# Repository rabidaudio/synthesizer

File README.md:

# Synth

> These are my custom modules for a from-scratch [Eurorack](https://en.wikipedia.org/wiki/Eurorack) analog synthesizer.

https://rabid.audio/projects/synth

## Modules

1. [Amplifier](amp)
  - LM13700
  - matched-pair PNP exponential converter
  - CV of 10V -> Gain=1
  - CV of <=0V -> Gain=\~0, 6 decades below Gain=1
  - allow overdrive to Gain=2
    - ideally this would begin to clip
  - mixdown
    - mono - full mix -> left and right
    - stereo split - A+C->left B+D->right
  - Direct stereo input jack
    - mix arbitrary signal with mixdown
    - e.g. for accepting signals from other synths
2. [Oscillator](vco)
  - 0-10V, 1V/octave, A0 to A10
  - Square/Triangle core via LM13700
  - Waveshapper for triangle -> sine
  - PWM control
    - triangle wave applied to comparator with CV controlling reference. Triangle wave means CV is linear
  - abs(triangle) can be used for 2x square
    - adds a lot of parts for little benefit
  - blending shapes isn't useful here, since we could use other oscillators for that
  - Option to sync with another osc?
    - in theory, grounding osc at a regular interval would reset the osc over and over, effectively changing it's frequency
  - CV control for shape?
  - Room for more shapes
    - white noise?
    - PDS
      - https://en.wikipedia.org/wiki/Phase_distortion_synthesis
      - a bit of wild harmonics
      - multiplication techniques
        - log/antilog
        - https://en.wikipedia.org/wiki/Gilbert_cell
        - AD633 ($11-$13 /unit on DigiKey!?)
        - EL4450C ($4/unit on Digikey but out of stock). It's a little more awkward to use since it's max differerential input voltage for linearity is 2V
      - the hard part will be the "slightly higher frequency" bit
        - perhaps instead you have another osc (555?) running at a fixed frequency and clipping the sine
        - square PWM control could also adjust this clip frequency
      - In Max you do PDS by `kink~`-ing a `phasor~` and using that to drive the phase of `cycle~`. Kink is somewhat straightforward to do - use a comparator to adjust the charge current after a threshold. But how you drive a sine wave phase with that I'm not sure
    - down ramp wave with just a JFET
      - up ramp wave probably needs another JFET and an inverter
    - sub octave
      - theory and example circuit: http://www.valvewizard.co.uk/uboat.html
    - octave
      - full wave rectifier
    - multiplying the triangle with a square wave with different phases and pulse-widths gives some neat sounds
    - polynomial
      - The EL4450C datasheet describes using a multiplier ic to create a polynomial of the form (k1 v^2 + v) / k2
      - it sounds like crap on a triangle wave and does nothing for a square wave, but it adds a nice second harmonic to a sine wave
      - from experiments in Max, good values are k1=1.5-2.5, k2=2
      - but at that point, should you just use 2 oscillators?
3. [A/D/S/R envelope](adsr)
  - 4 envelopes required for 4-voice polyphony
  - wired to VCA by default
  - save surface area with 1 set of ADSR controls for a pair of envelopes
  - fully modular means you could borrow one for VCF instead, or send to both VCA and VCF
4. Filter
  -  4P LP(/HP?)
  - Cutoff frequency control has same range as oscillator
    - 0-10V, 1V/octave, A0 to A10
  - filter we designed for class
    - standard vactrols are available on Thonk
  - CV control of cutoff + resonance
  - Default to track cutoff with VCO-CV
  - individual filter knobs, plus a global knob for filter sweeps
5. [Utilities](utils)
  - Buffer, Sum, Attenuate, Invert, Gate
  - Could be all-in one
    - A input (default ground)
    - B input (default ground)
    - level knob attenuator
    - gate digital CV in, default on
    - `(A+B)*level*gate` output
    - `-(A+B)*level*gate` output
    - Constant CV out if A and B disconnected

Bitcrusher?
4 filters or one?
Noise?
Clock?
Headphone output no longer required
2D mixer?

## TODO

- utility module
  - [x] Verify on breadboard
  - [x] design PCB
  - [x] order parts
  - [x] come up with a cute name
  - [x] design front panel
  - [x] assemble Rev. A PCB
    - bend the regulators first
    - plenty of 4066s
    - flip orientation of power connector
    - pot orientation - both channels:
      - right side (facing) to inside of board (from top)
      - left side (facing) to outside of board (from top)
  - [x] test with Neutron
    - constant output is only 9 to -7.8
    - high noise when used as a buffer
      - perhaps input signal is clipping?
      - white noise when the gain is turned down
  - [x] adjust design for Rev. B
  - [x] assemble Rev. B proto board
  - fix prototype issues
    - [ ] sum pot is backwards
    - [ ] a bit of noise on the constant output near the center
    - [ ] verify output levels
    - [ ] hard click on gate
      - needs a LPF?
  - [ ] assemble Rev. B PCB
  - [ ] manufacture front panel
  - [ ] assemble module
- VCA
  - [x] Confirm amp on breadboard, finalize CV levels
  - [x] figure out where tuning trimmers are needed
  - [x] build prototype
  - fix prototype issues
    - [ ] output is too quiet for headphones, need about 2x gain
    - [ ] CV range is too wide, adjust scaling for faster change in db/V
  - [ ] finish PCB schematic for complete amplifier
  - [ ] Create PCB
  - [ ] design front panel
  - [ ] manufacture front panel
  - [ ] assemble module
- VCO
  - [ ] design core
    - [x] core osc - square/triangle
    - [x] wave shaper (sine)
    - [x] pwm control
    - [ ] additional shape
    - [x] shape selection
  - [x] Confirm amp on breadboard, finalize CV levels
  - fix breadboard test issues
    - [ ] pitch is very sensitive to power supply noise
    - [ ] tuning is rather difficult
  - [ ] Build prototype
  - fix prototype issues
    - TBD
  - [ ] design PCB
  - [ ] Create PCB
  - [ ] design front panel
  - [ ] manufacture front panel
  - [ ] assemble module
- Envelope
  - [x] design in SPICE
  - [ ] verify on breadboard
  - [ ] build prototype
  - fix prototype issues
    - TBD
  - [ ] design PCB
  - [ ] Create PCB
  - [ ] design front panel
  - [ ] manufacture front panel
  - [ ] assemble module
- VCF
  - TBD
- build tools
  - [x] tiny Breakout pcbs for headphone jacks
  - ~~transistor matcher circuit~~
    - bought matched pair BJTs instead
  - [x] quantized selector with hysteresis

## License

Schematics, board layouts, documentation, etc. is licensed under [Creative Commons Attribution-NonCommercial-ShareAlike 4.0 International License](http://creativecommons.org/licenses/by-nc-sa/4.0/).

If you're interested in commercial use, please ask first.

Any source code is licensed under [MIT](SOFTWARE_LICENSE).

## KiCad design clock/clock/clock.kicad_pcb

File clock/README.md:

# The Count

## [Writeup and documentation](https://rabid.audio/projects/synth/clk/)

## Features

- BPM from 15 to 400
- two outputs with relative rates
- 3-digit LED 7-segment display
- swing control
- tap tempo
- CV in
- pause
- save/load/reset settings

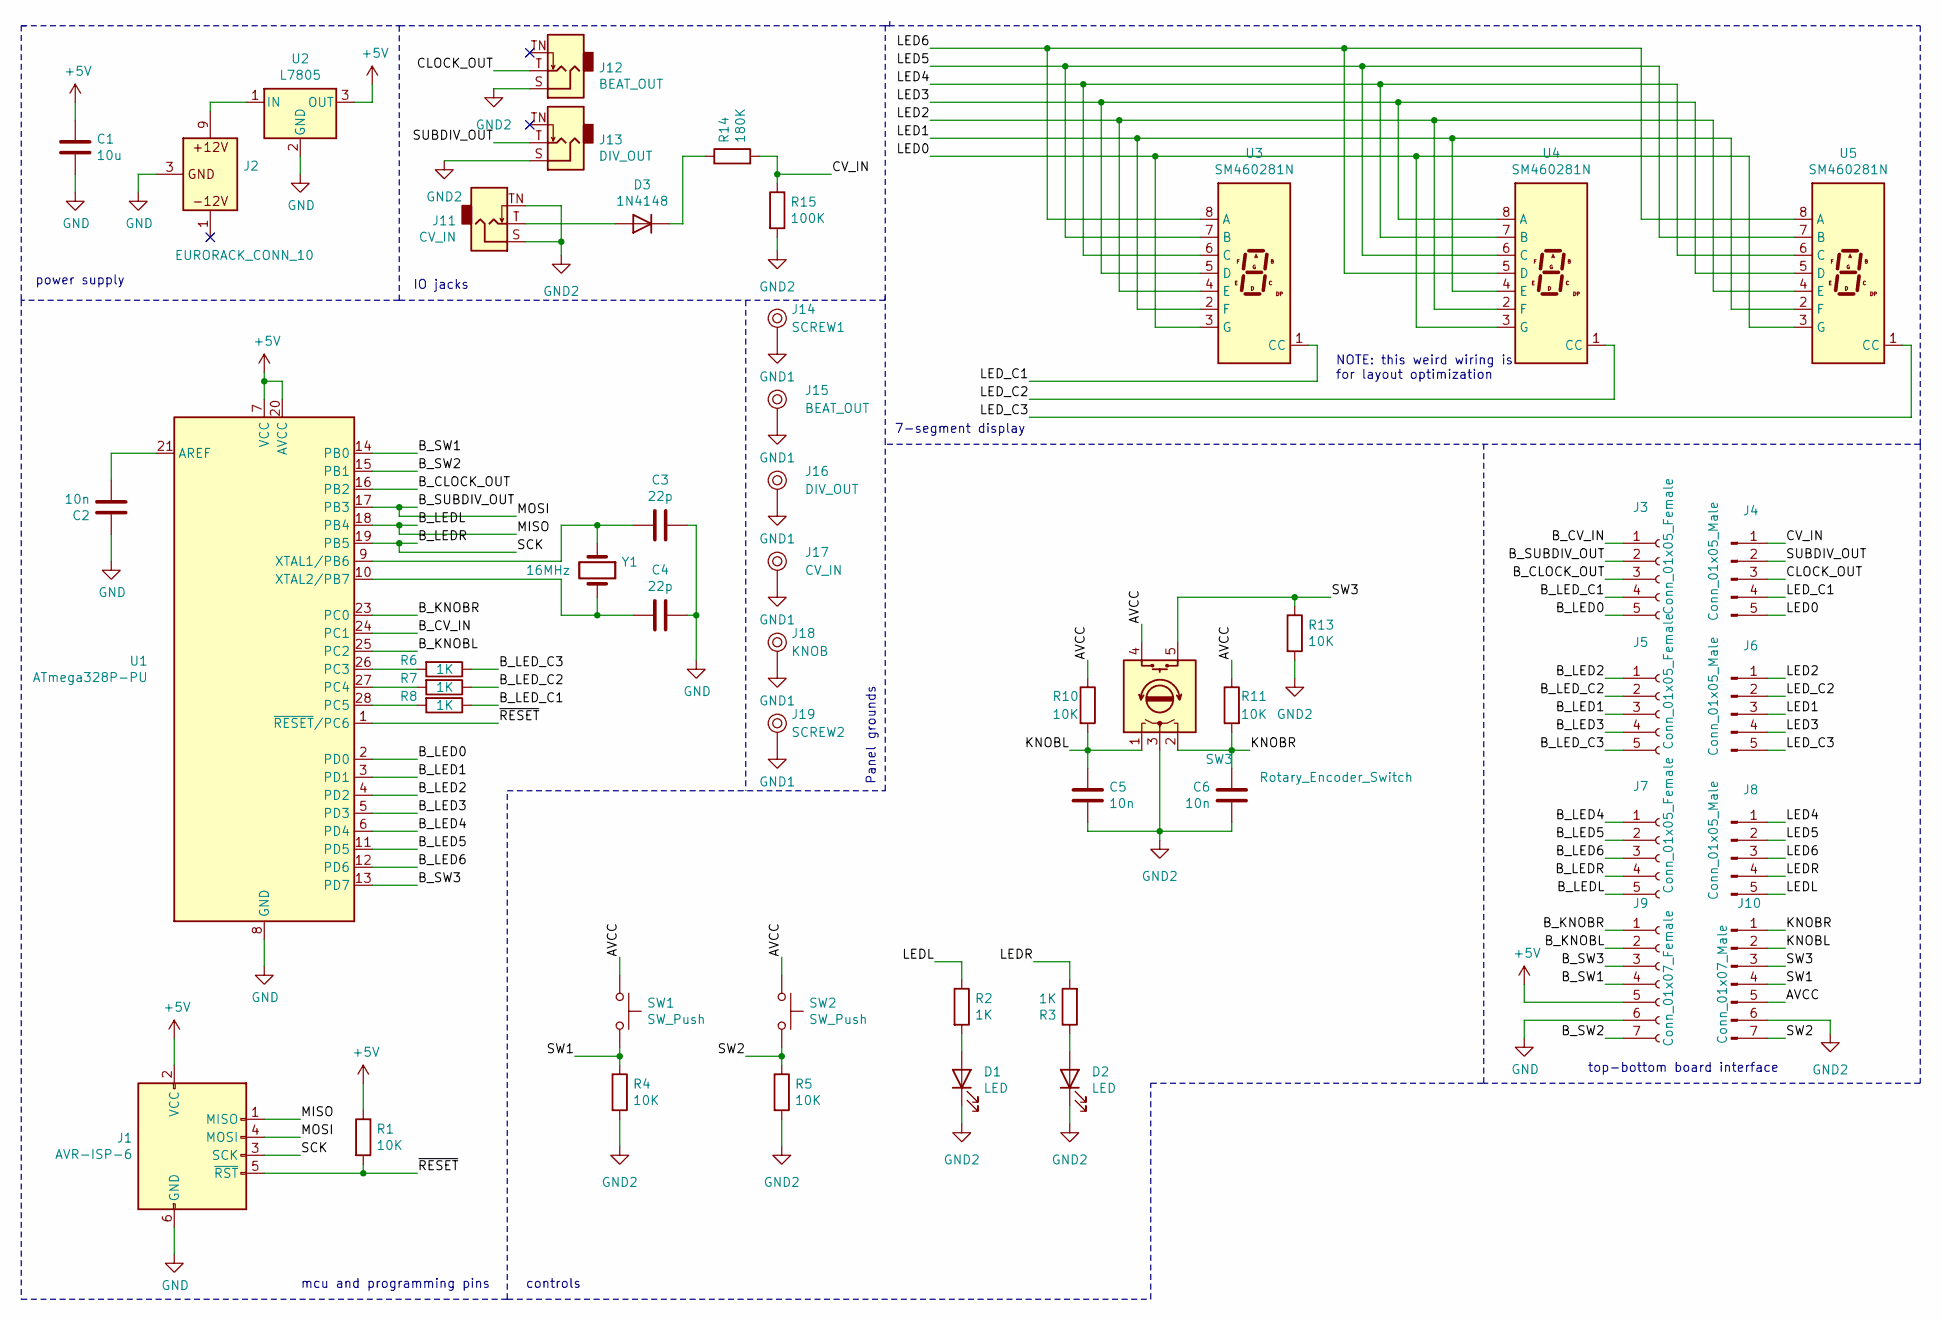
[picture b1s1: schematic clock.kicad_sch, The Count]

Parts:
C1: 10u; CP_Radial_Tantal_D4.5mm_P2.50mm
C2, C5, C6: 10n; C_Rect_L7.0mm_W3.5mm_P5.00mm
C3, C4: 22p; C_Rect_L7.0mm_W3.5mm_P5.00mm
D1, D2: LED; LED_D3.0mm
D3: 1N4148; D_T-1_P5.08mm_Horizontal
J1: AVR-ISP-6; PinHeader_2x03_P2.54mm_Vertical
J2: EURORACK_CONN_10; EURORACK_10_IDC
J3, J5, J7: Conn_01x05_Female; PinSocket_1x05_P2.54mm_Vertical
J4, J6, J8: Conn_01x05_Male; PinHeader_1x05_P2.54mm_Vertical
J9: Conn_01x07_Female; PinSocket_1x07_P2.54mm_Vertical
J10: Conn_01x07_Male; PinHeader_1x07_P2.54mm_Vertical
J11: CV_IN; Jack_3.5mm_QingPu_WQP-PJ398SM_Vertical_CircularHoles
J12: BEAT_OUT; Jack_3.5mm_QingPu_WQP-PJ398SM_Vertical_CircularHoles
J13: DIV_OUT; Jack_3.5mm_QingPu_WQP-PJ398SM_Vertical_CircularHoles
J14: SCREW1; eurorack_screw_hole
J15: BEAT_OUT; thonkiconn_hole
J16: DIV_OUT; thonkiconn_hole
J17: CV_IN; thonkiconn_hole
J18: KNOB; knob_hole
J19: SCREW2; eurorack_screw_hole
R1, R4, R5, R10, R11, R13: 10K; R_Axial_DIN0207_L6.3mm_D2.5mm_P2.54mm_Vertical
R2, R3, R6, R7, R8: 1K; R_Axial_DIN0207_L6.3mm_D2.5mm_P2.54mm_Vertical
R14: 180K; R_Axial_DIN0207_L6.3mm_D2.5mm_P2.54mm_Vertical
R15: 100K; R_Axial_DIN0207_L6.3mm_D2.5mm_P2.54mm_Vertical
SW1, SW2: SW_Push; SW_PUSH_6mm
SW3: Rotary_Encoder_Switch; RotaryEncoder_Bourns_PEC11R_Vertical_Switch
U1: ATmega328P-PU; DIP-28_W7.62mm
U2: L7805; TO-220-3_Vertical
U3, U4, U5: SM460281N; SM460281N_ARKLED_0.28mm_CC_7-segment_LED
Y1: 16MHz; Crystal_HC50_Vertical

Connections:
+5V: C1.1, J1.2 (VCC), J9.5, R1.1, U1.7 (VCC), U1.20 (AVCC), U2.3 (OUT)
/AVCC: J10.5, R10.1, R11.1, SW1.1, SW2.1, SW3.4 (S1)
/B_CLOCK_OUT: J3.3, U1.16 (PB2)
/B_CV_IN: J3.1, U1.24 (PC1)
/B_KNOBL: J9.2, U1.25 (PC2)
/B_KNOBR: J9.1, U1.23 (PC0)
/B_LED0: J3.5, U1.2 (PD0)
/B_LED1: J5.3, U1.3 (PD1)
/B_LED2: J5.1, U1.4 (PD2)
/B_LED3: J5.4, U1.5 (PD3)
/B_LED4: J7.1, U1.6 (PD4)
/B_LED5: J7.2, U1.11 (PD5)
/B_LED6: J7.3, U1.12 (PD6)
/B_LEDL: J1.1 (MISO), J7.5, U1.18 (PB4)
/B_LEDR: J1.3 (SCK), J7.4, U1.19 (PB5)
/B_LED_C1: J3.4, R8.1
/B_LED_C2: J5.2, R7.1
/B_LED_C3: J5.5, R6.1
/B_SUBDIV_OUT: J1.4 (MOSI), J3.2, U1.17 (PB3)
/B_SW1: J9.4, U1.14 (PB0)
/B_SW2: J9.7, U1.15 (PB1)
/B_SW3: J9.3, U1.13 (PD7)
/CLOCK_OUT: J4.3, J12.T
/CV_IN: J4.1, R14.2, R15.1
/KNOBL: C5.1, J10.2, R10.2, SW3.1 (A)
/KNOBR: C6.1, J10.1, R11.2, SW3.2 (B)
/LED0: J4.5, U3.3 (G), U4.3 (G), U5.3 (G)
/LED1: J6.3, U3.2 (F), U4.4 (E), U5.2 (F)
/LED2: J6.1, U3.4 (E), U4.2 (F), U5.4 (E)
/LED3: J6.4, U3.5 (D), U4.8 (A), U5.5 (D)
/LED4: J8.1, U3.6 (C), U4.7 (B), U5.6 (C)
/LED5: J8.2, U3.7 (B), U4.6 (C), U5.7 (B)
/LED6: J8.3, U3.8 (A), U4.5 (D), U5.8 (A)
/LEDL: J8.5, R2.1
/LEDR: J8.4, R3.2
/LED_C1: J4.4, U3.1 (CC)
/LED_C2: J6.2, U4.1 (CC)
/LED_C3: J6.5, U5.1 (CC)
/SUBDIV_OUT: J4.2, J13.T
/SW1: J10.4, R4.1, SW1.2
/SW2: J10.7, R5.1, SW2.2
/SW3: J10.3, R13.1, SW3.5 (S2)
/~RESET: J1.5 (~RST), R1.2, U1.1 (~RESET/PC6)
GND: C1.2, C2.1, C3.1, C4.1, J1.6 (GND), J2.3 (GND), J9.6, U1.8 (GND), U1.22 (GND), U2.2 (GND)
GND1: J14.1, J15.1, J16.1, J17.1, J18.1, J19.1
GND2: C5.2, C6.2, D1.1 (K), D2.1 (K), J10.6, J11.S, J11.TN, J12.S, J13.S, R4.2, R5.2, R13.2, R15.2, SW3.3 (C)
unnamed: C2.2, U1.21 (AREF)
unnamed: C3.2, U1.9 (XTAL1/PB6), Y1.1
unnamed: C4.2, U1.10 (XTAL2/PB7), Y1.2
unnamed: D1.2 (A), R2.2
unnamed: D2.2 (A), R3.1
unnamed: D3.1 (K), R14.1
unnamed: D3.2 (A), J11.T
unnamed: J2.9 (12V_P), U2.1 (IN)
unnamed: R6.2, U1.26 (PC3)
unnamed: R7.2, U1.27 (PC4)
unnamed: R8.2, U1.28 (PC5)

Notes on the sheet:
NOTE: this weird wiring is for layout optimization
7-segment display
Panel grounds
top-bottom board interface
power supply
mcu and programming pins
IO jacks
controls

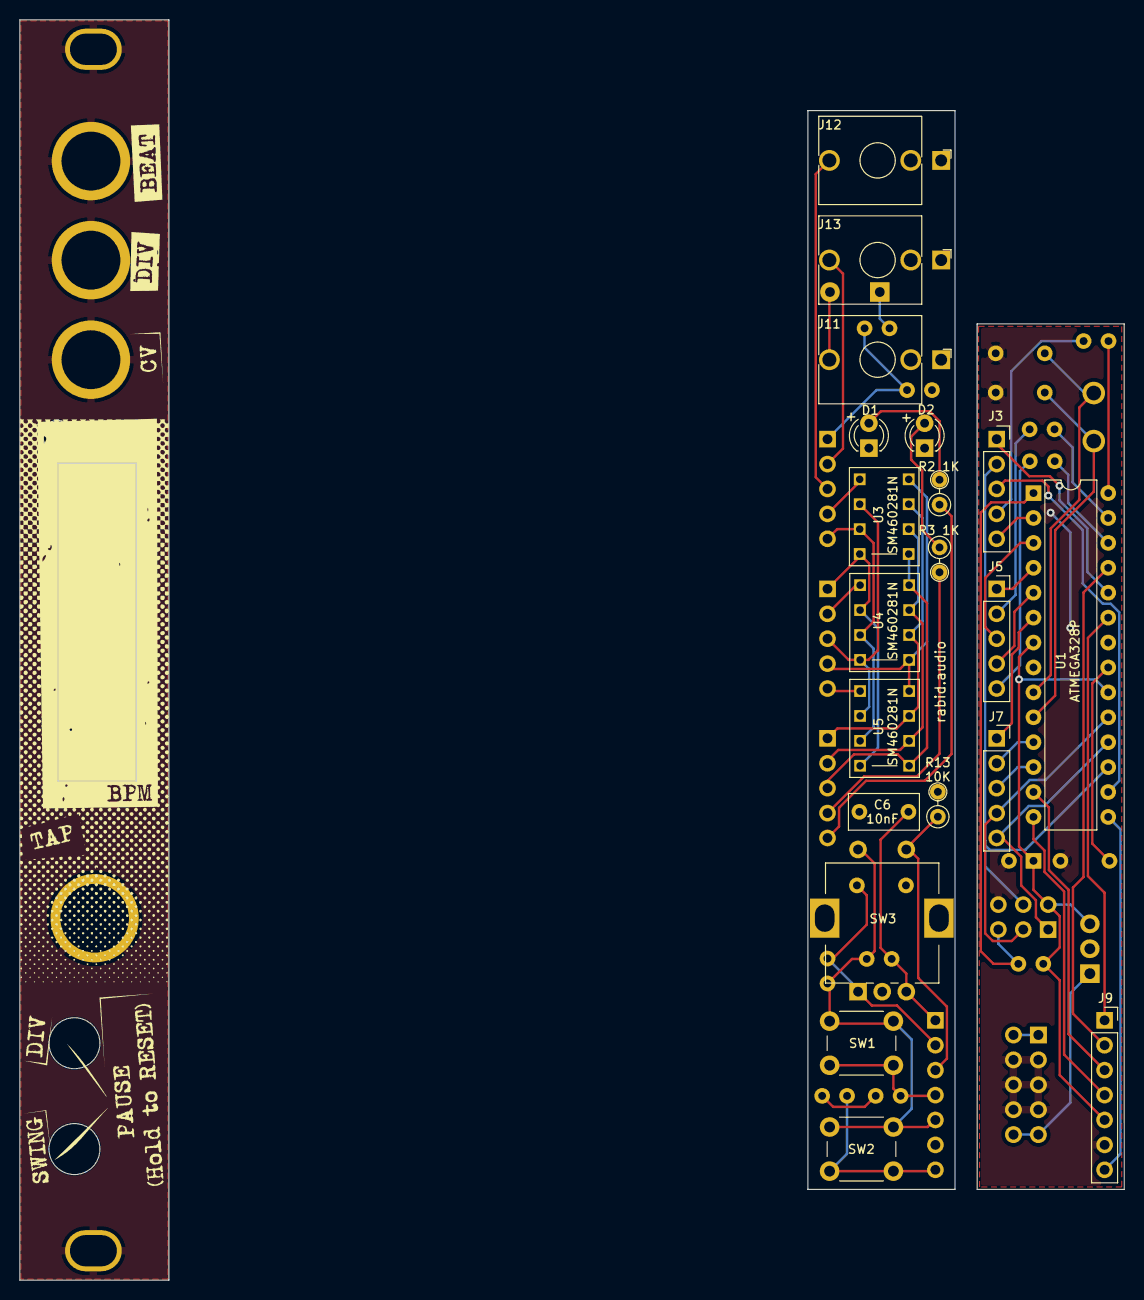
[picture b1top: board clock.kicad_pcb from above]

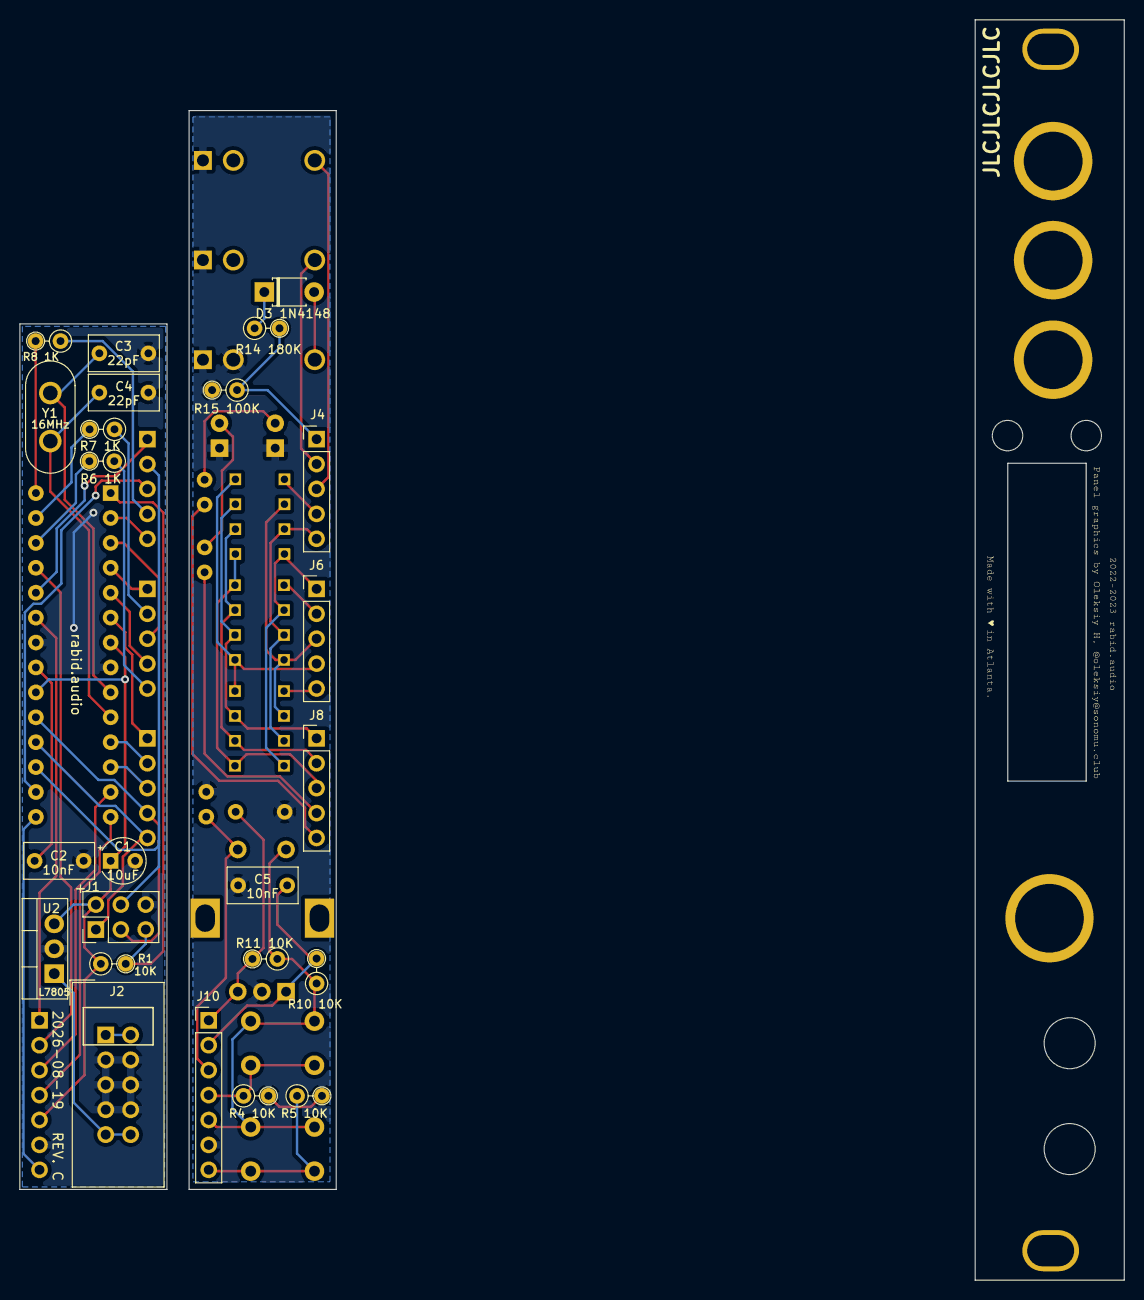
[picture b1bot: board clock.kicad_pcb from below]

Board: 2 copper layers, 112.6 x 128.5 mm, 50 parts (24 on the bottom side), 57 nets.

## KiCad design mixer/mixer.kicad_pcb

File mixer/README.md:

6-8 channels

vertical faders
Mute and solo buttons

stereo and pan?

Aux send/return (x2?)
EQ?

No CV?

Digital

cypress?

Op-amps in, round-robin sampling? Codec?

Per channel:
- in jack
- Fader
- mute btn+led
- solo btn+led
- Aux send knob
- Pan knob
- Tone knob (center detent)

Master:
- aux return jack x2
- out jack x2
- fader
- Aux return knob

maybe sets of 4 channels, plus master - with ribbon
- each has a single mix with direct in mixdown, allowing infinite daisy chain
  - -> prev in x2
  - mixdown x2 ->
  - mute/solo bus - SPI? <->
  - Power (from master)

- Master is analog mixer: last mixdown plus aux, through master fader and out

M_Switch
S_Switch
~Global_Solo (open drain, low if any solos)

M_LED = M_Switch && ~Global_Solo
S_LED = S_Switch
Global_Solo = Global_Solo || S_Switch
Channel Muted = M_Switch || (Global_Solo && !S_Switch)

https://docs.google.com/spreadsheets/d/1g7xjcmLrPR7thaU7WiNtqLLgusEtm41Zfw6h4pZd12A/edit?gid=347525464#gid=347525464

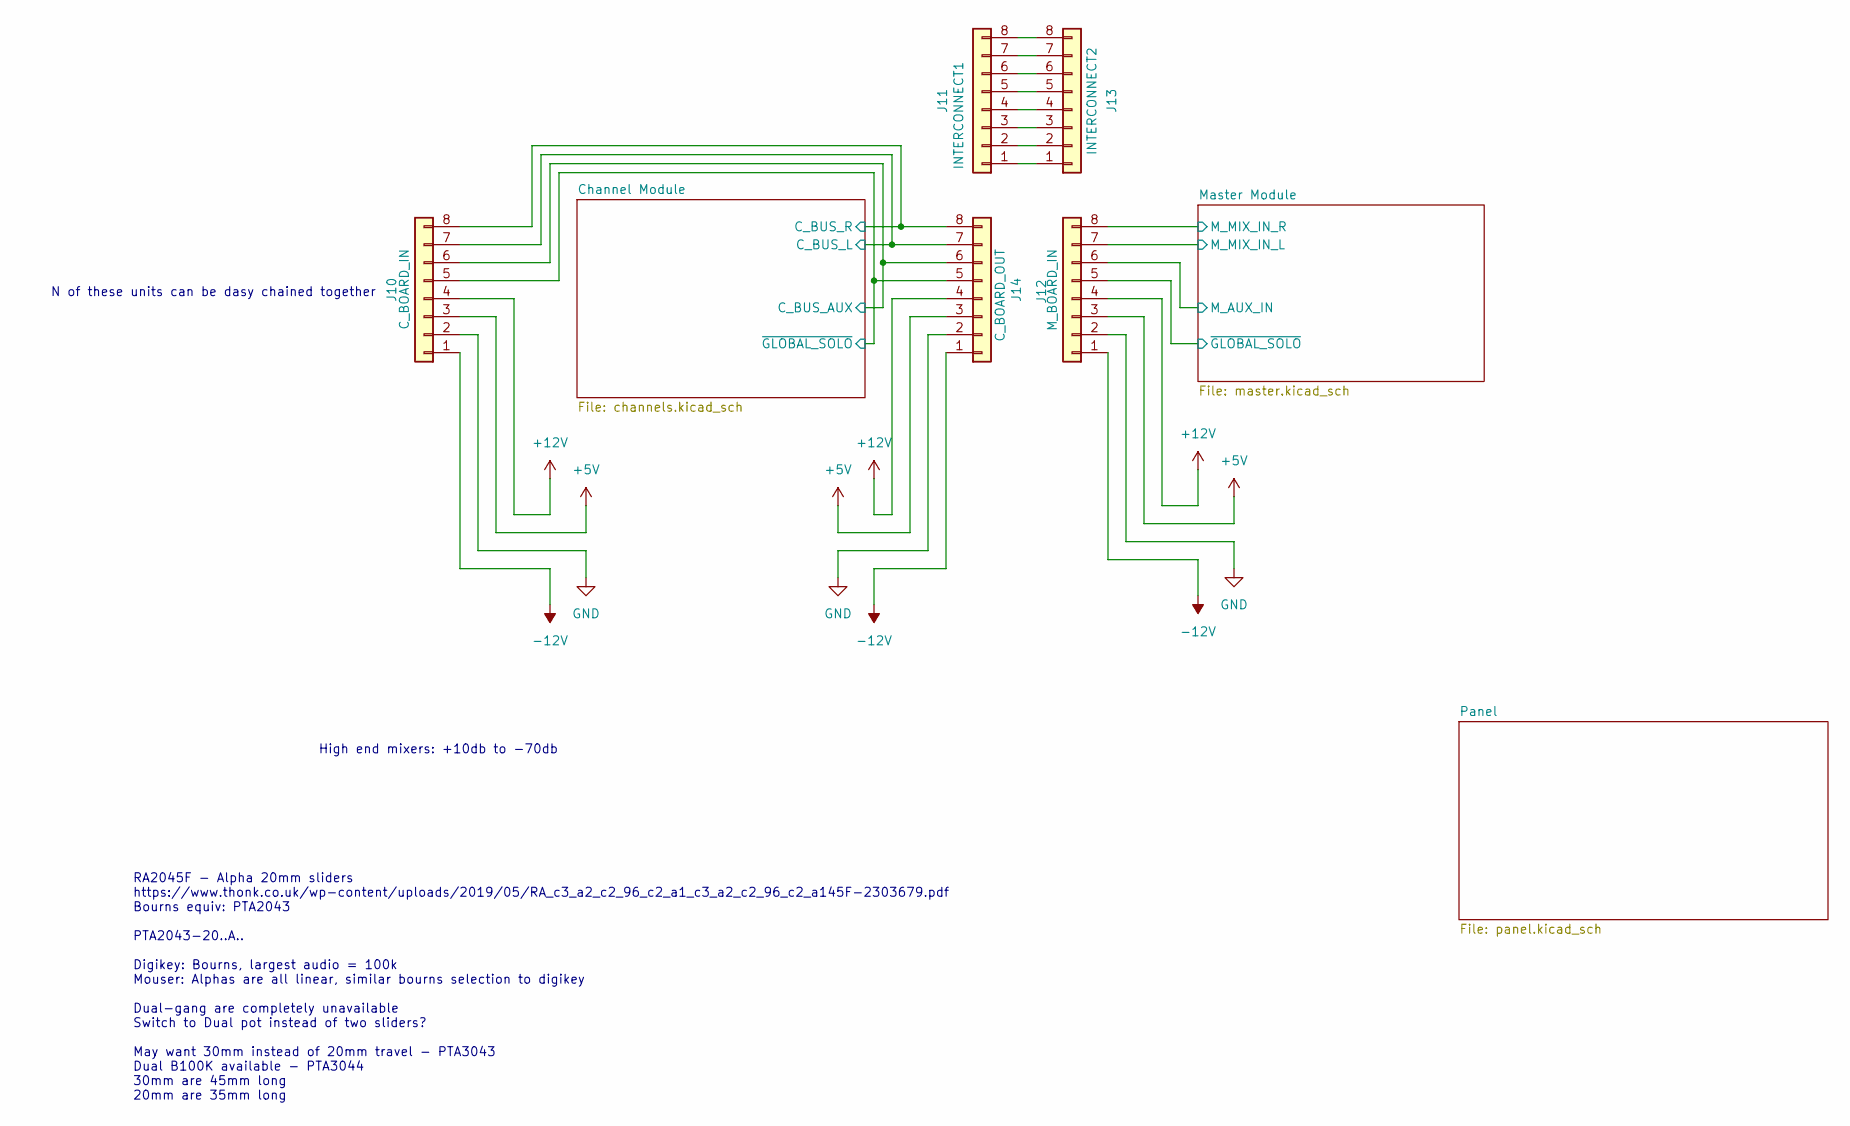
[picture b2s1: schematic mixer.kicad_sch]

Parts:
J10: C_BOARD_IN; PinSocket_1x08_P1.27mm_Vertical
J11: INTERCONNECT1; PinHeader_1x08_P1.27mm_Vertical
J12: M_BOARD_IN; PinSocket_1x08_P1.27mm_Vertical
J13: INTERCONNECT2; PinHeader_1x08_P1.27mm_Vertical
J14: C_BOARD_OUT; PinSocket_1x08_P1.27mm_Vertical

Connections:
+5V: J10.3, J12.3, J14.3; also elsewhere on the board
+12V: J10.4, J12.4, J14.4; also elsewhere on the board
-12V: J10.1, J12.1, J14.1; also elsewhere on the board
/Channel Module/C_BUS_AUX: J10.6, J14.6; also elsewhere on the board
/Channel Module/C_BUS_L: J10.7, J14.7; also elsewhere on the board
/Channel Module/C_BUS_R: J10.8, J14.8; also elsewhere on the board
/Channel Module/~GLOBAL_SOLO: J10.5, J14.5; also elsewhere on the board
/Master Module/M_AUX_IN: J12.6; also elsewhere on the board
/Master Module/M_MIX_IN_L: J12.7; also elsewhere on the board
/Master Module/M_MIX_IN_R: J12.8; also elsewhere on the board
/Master Module/~GLOBAL_SOLO: J12.5; also elsewhere on the board
GND: J10.2, J12.2, J14.2; also elsewhere on the board
unnamed: J11.1, J13.1
unnamed: J11.2, J13.2
unnamed: J11.3, J13.3
unnamed: J11.4, J13.4
unnamed: J11.5, J13.5
unnamed: J11.6, J13.6
unnamed: J11.7, J13.7
unnamed: J11.8, J13.8

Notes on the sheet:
High end mixers: +10db to -70db
RA2045F - Alpha 20mm sliders https://www.thonk.co.uk/wp-content/uploads/2019/05/RA_c3_a2_c2_96_c2_a1_c3_a2_c2_96_c2_a145F-2303679.pdf Bourns equiv: PTA2043 PTA2043-20..A.. Digikey: Bourns, largest audio = 100k Mouser: Alphas are all linear, similar bourns selection to digikey Dual-gang are complete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
N of these units can be dasy chained together

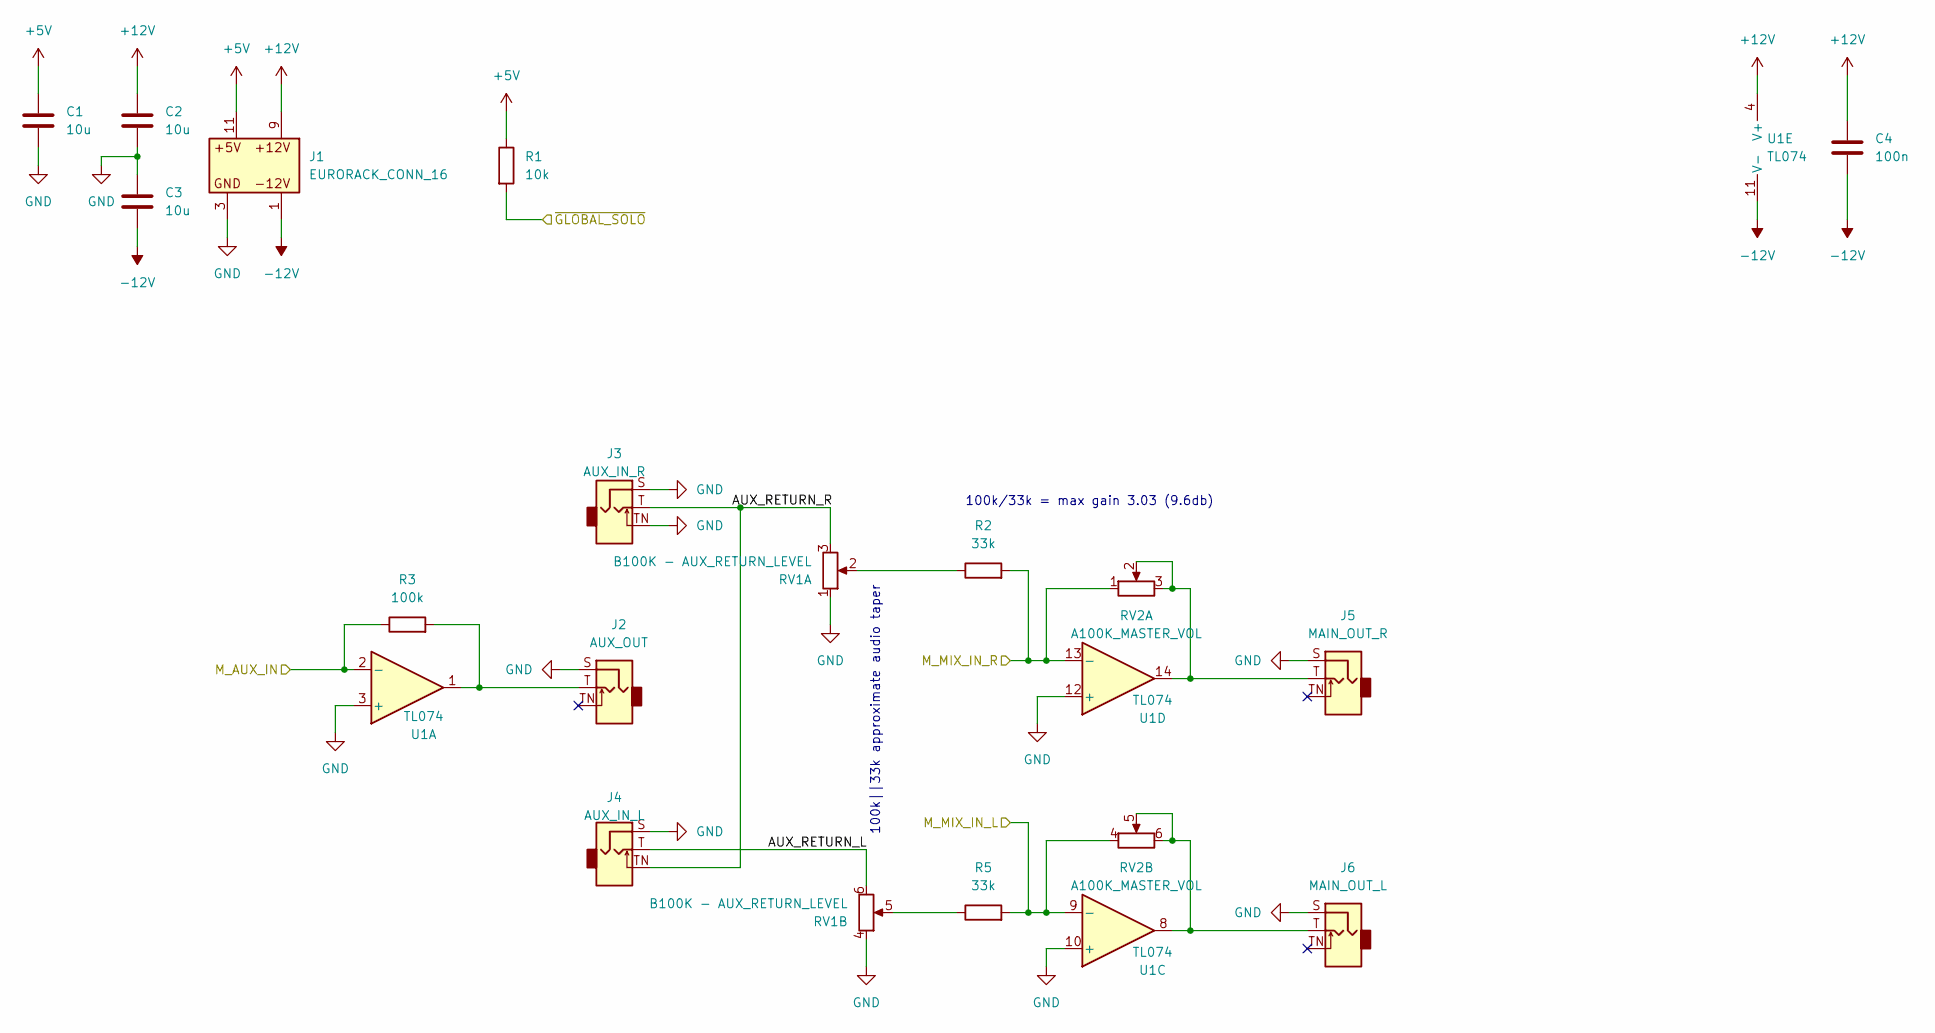
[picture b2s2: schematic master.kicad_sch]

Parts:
C1, C2, C3: 10u; C_0603_1608Metric
C4: 100n; C_0603_1608Metric
J1: EURORACK_CONN_16; EURORACK_16_IDC
J2: AUX_OUT; Jack_3.5mm_QingPu_WQP-PJ398SM_Vertical_CircularHoles
J3: AUX_IN_R; Jack_3.5mm_QingPu_WQP-PJ398SM_Vertical_CircularHoles
J4: AUX_IN_L; Jack_3.5mm_QingPu_WQP-PJ398SM_Vertical_CircularHoles
J5: MAIN_OUT_R; Jack_3.5mm_QingPu_WQP-PJ398SM_Vertical_CircularHoles
J6: MAIN_OUT_L; Jack_3.5mm_QingPu_WQP-PJ398SM_Vertical_CircularHoles
R1: 10k; R_0603_1608Metric
R2, R5: 33k; R_0603_1608Metric
R3: 100k; R_0603_1608Metric
RV1: B100K - AUX_RETURN_LEVEL; Potentiometer_Alpha_RD902F-40-00D_Dual_Vertical_CircularHol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
RV2: A100K_MASTER_VOL; Potentiometer_Alpha_RD902F-40-00D_Dual_Vertical_CircularHol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
U1: TL074; SOIC-14_3.9x8.7mm_P1.27mm

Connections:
+5V: C1.1, J1.11 (5V), R1.1; also elsewhere on the board
+12V: C2.1, C4.1, J1.9 (12V_P), U1.4 (V+); also elsewhere on the board
-12V: C3.2, C4.2, J1.1 (12V_N), U1.11 (V-); also elsewhere on the board
/Master Module/AUX_RETURN_L: J4.T, RV1.6
/Master Module/AUX_RETURN_R: J3.T, J4.TN, RV1.3
/Master Module/M_AUX_IN: R3.1, U1.2 (-); also elsewhere on the board
/Master Module/M_MIX_IN_L: R5.2, RV2.4, U1.9 (-); also elsewhere on the board
/Master Module/M_MIX_IN_R: R2.2, RV2.1, U1.13 (-); also elsewhere on the board
/Master Module/~GLOBAL_SOLO: R1.2; also elsewhere on the board
GND: C1.2, C2.2, C3.1, J1.3 (GND), J2.S, J3.S, J3.TN, J4.S, J5.S, J6.S, RV1.1, RV1.4, U1.3 (+), U1.10 (+), U1.12 (+); also elsewhere on the board
unnamed: J2.T, R3.2, U1.1
unnamed: J5.T, RV2.2, RV2.3, U1.14
unnamed: J6.T, RV2.5, RV2.6, U1.8
unnamed: R2.1, RV1.2
unnamed: R5.1, RV1.5

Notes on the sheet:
100k||33k approximate audio taper
100k/33k = max gain 3.03 (9.6db)

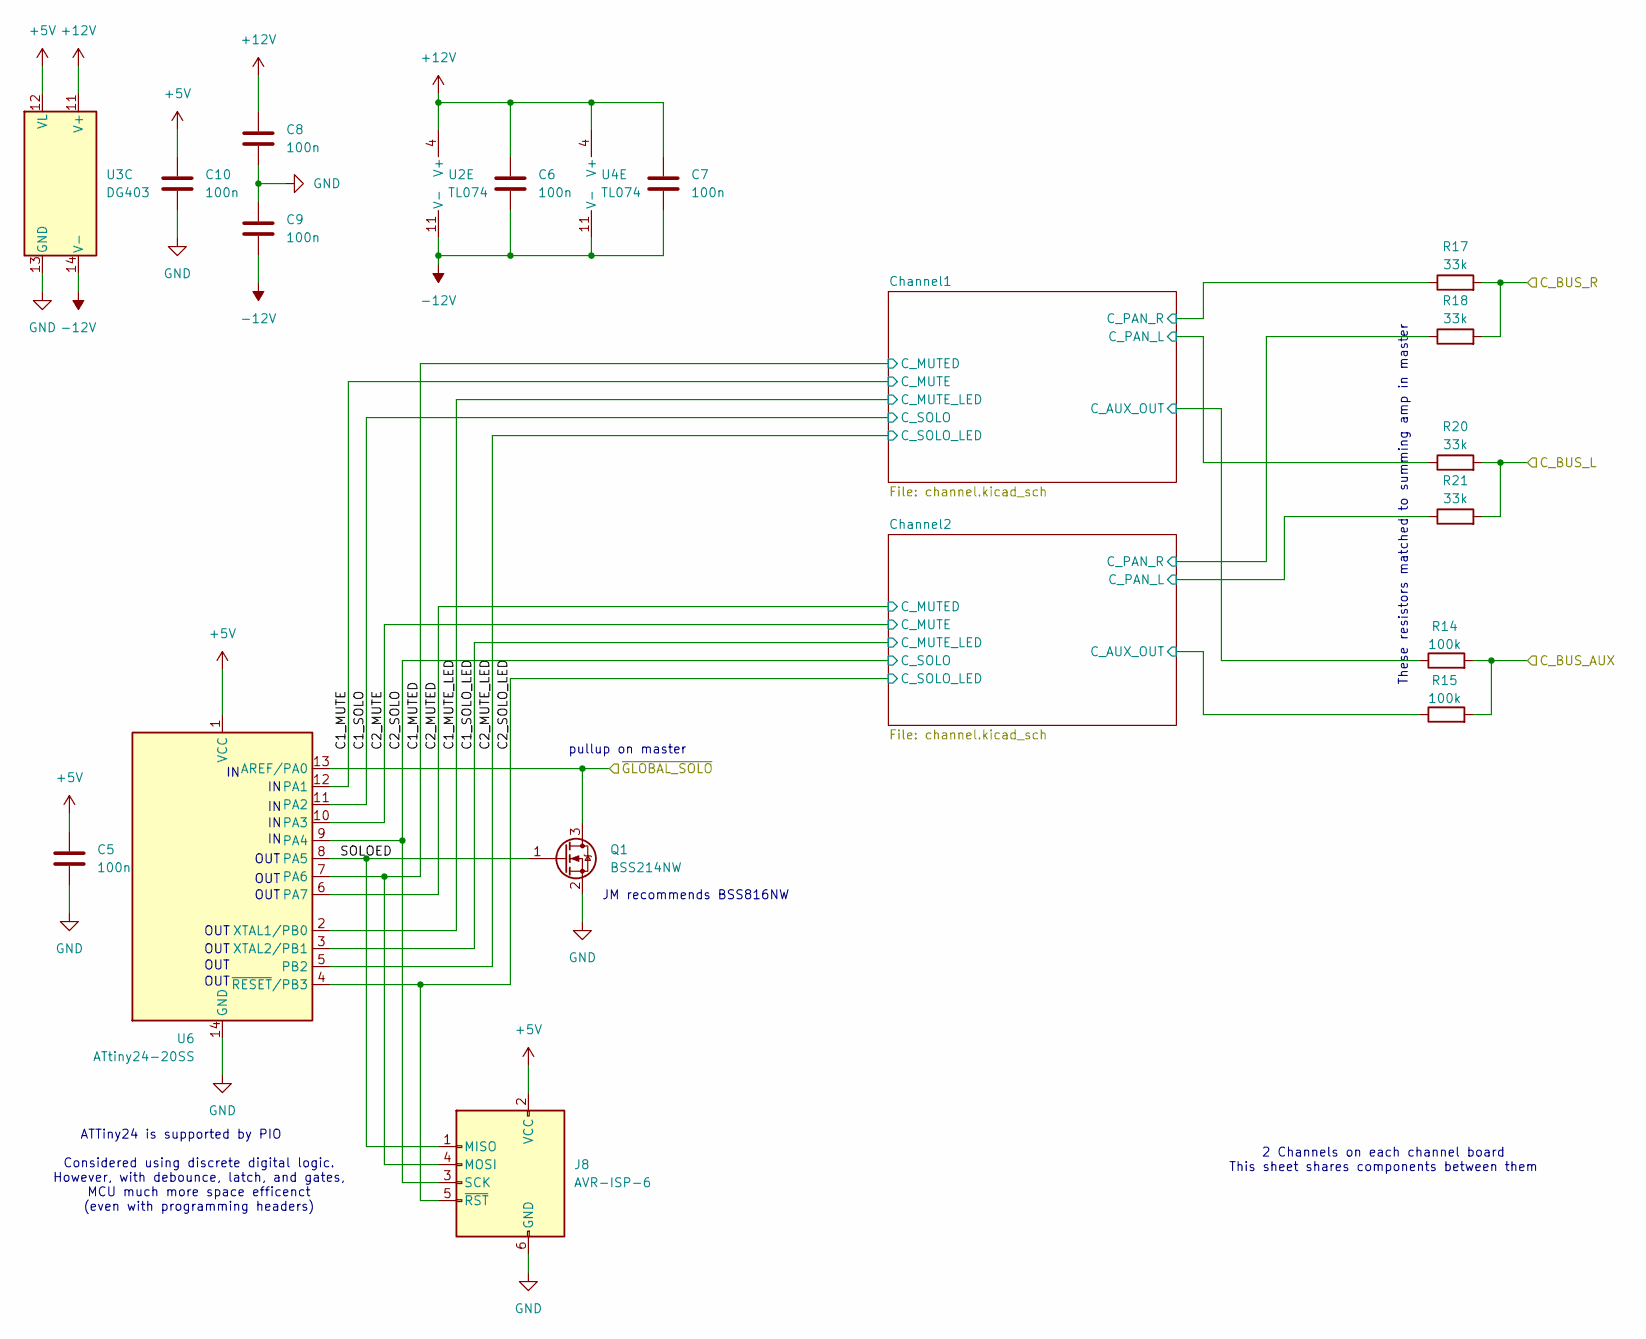
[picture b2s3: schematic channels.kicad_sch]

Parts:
C5, C6, C7, C8, C9, C10: 100n; C_0603_1608Metric
J8: AVR-ISP-6; IVR_PADS
Q1: BSS214NW; SOT-323_SC-70
R14, R15: 100k; R_0603_1608Metric
R17, R18, R20, R21: 33k; R_0603_1608Metric
U2, U4: TL074; SOIC-14_3.9x8.7mm_P1.27mm
U3: DG403; SOIC-16_3.9x9.9mm_P1.27mm
U6: ATtiny24-20SS; SOIC-14_3.9x8.7mm_P1.27mm

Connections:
+5V: C5.1, C10.1, J8.2 (VCC), U3.12 (VL), U6.1 (VCC); also elsewhere on the board
+12V: C6.1, C7.1, C8.1, U2.4 (V+), U3.11 (V+), U4.4 (V+); also elsewhere on the board
-12V: C6.2, C7.2, C9.2, U2.11 (V-), U3.14 (V-), U4.11 (V-); also elsewhere on the board
/Channel Module/C1_MUTE: U6.12 (PA1); also elsewhere on the board
/Channel Module/C1_MUTED: J8.4 (MOSI), U6.7 (PA6); also elsewhere on the board
/Channel Module/C1_MUTE_LED: U6.2 (XTAL1/PB0); also elsewhere on the board
/Channel Module/C1_SOLO: U6.11 (PA2); also elsewhere on the board
/Channel Module/C1_SOLO_LED: U6.3 (XTAL2/PB1); also elsewhere on the board
/Channel Module/C2_MUTE: U6.10 (PA3); also elsewhere on the board
/Channel Module/C2_MUTED: U3.10 (IN2), U6.6 (PA7); also elsewhere on the board
/Channel Module/C2_MUTE_LED: U6.5 (PB2); also elsewhere on the board
/Channel Module/C2_SOLO: J8.3 (SCK), U6.9 (PA4); also elsewhere on the board
/Channel Module/C2_SOLO_LED: J8.5 (~RST), U6.4 (~RESET/PB3); also elsewhere on the board
/Channel Module/C_BUS_AUX: R14.2, R15.2; also elsewhere on the board
/Channel Module/C_BUS_L: R20.2, R21.2; also elsewhere on the board
/Channel Module/C_BUS_R: R17.2, R18.2; also elsewhere on the board
/Channel Module/Channel1/C_AUX_OUT: R14.1; also elsewhere on the board
/Channel Module/Channel1/C_PAN_L: R20.1; also elsewhere on the board
/Channel Module/Channel1/C_PAN_R: R17.1; also elsewhere on the board
/Channel Module/Channel2/C_AUX_OUT: R15.1; also elsewhere on the board
/Channel Module/Channel2/C_PAN_L: R21.1, U2.1, U2.2 (-)
/Channel Module/Channel2/C_PAN_R: R18.1, U2.6 (-), U2.7
/Channel Module/SOLOED: J8.1 (MISO), Q1.1 (G), U6.8 (PA5)
/Channel Module/~GLOBAL_SOLO: Q1.3 (D), U6.13 (AREF/PA0); also elsewhere on the board
GND: C5.2, C8.2, C9.1, C10.2, J8.6 (GND), Q1.2 (S), U3.13 (GND), U4.3 (+), U6.14 (GND); also elsewhere on the board
unnamed 55: U3.5 (S4); also elsewhere on the board
unnamed 57: U4.6 (-), U4.7; also elsewhere on the board
unnamed 58: U2.3 (+); also elsewhere on the board
unnamed 59: U2.5 (+); also elsewhere on the board
unnamed 63: U3.6 (D4), U4.1; also elsewhere on the board
unnamed 64: U4.2 (-); also elsewhere on the board
unnamed 65: U4.5 (+); also elsewhere on the board

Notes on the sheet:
2 Channels on each channel board This sheet shares components between them
OUT
Considered using discrete digital logic. However, with debounce, latch, and gates, MCU much more space efficenct (even with programming headers)
These resistors matched to summing amp in master
pullup on master
ATTiny24 is supported by PIO
JM recommends BSS816NW

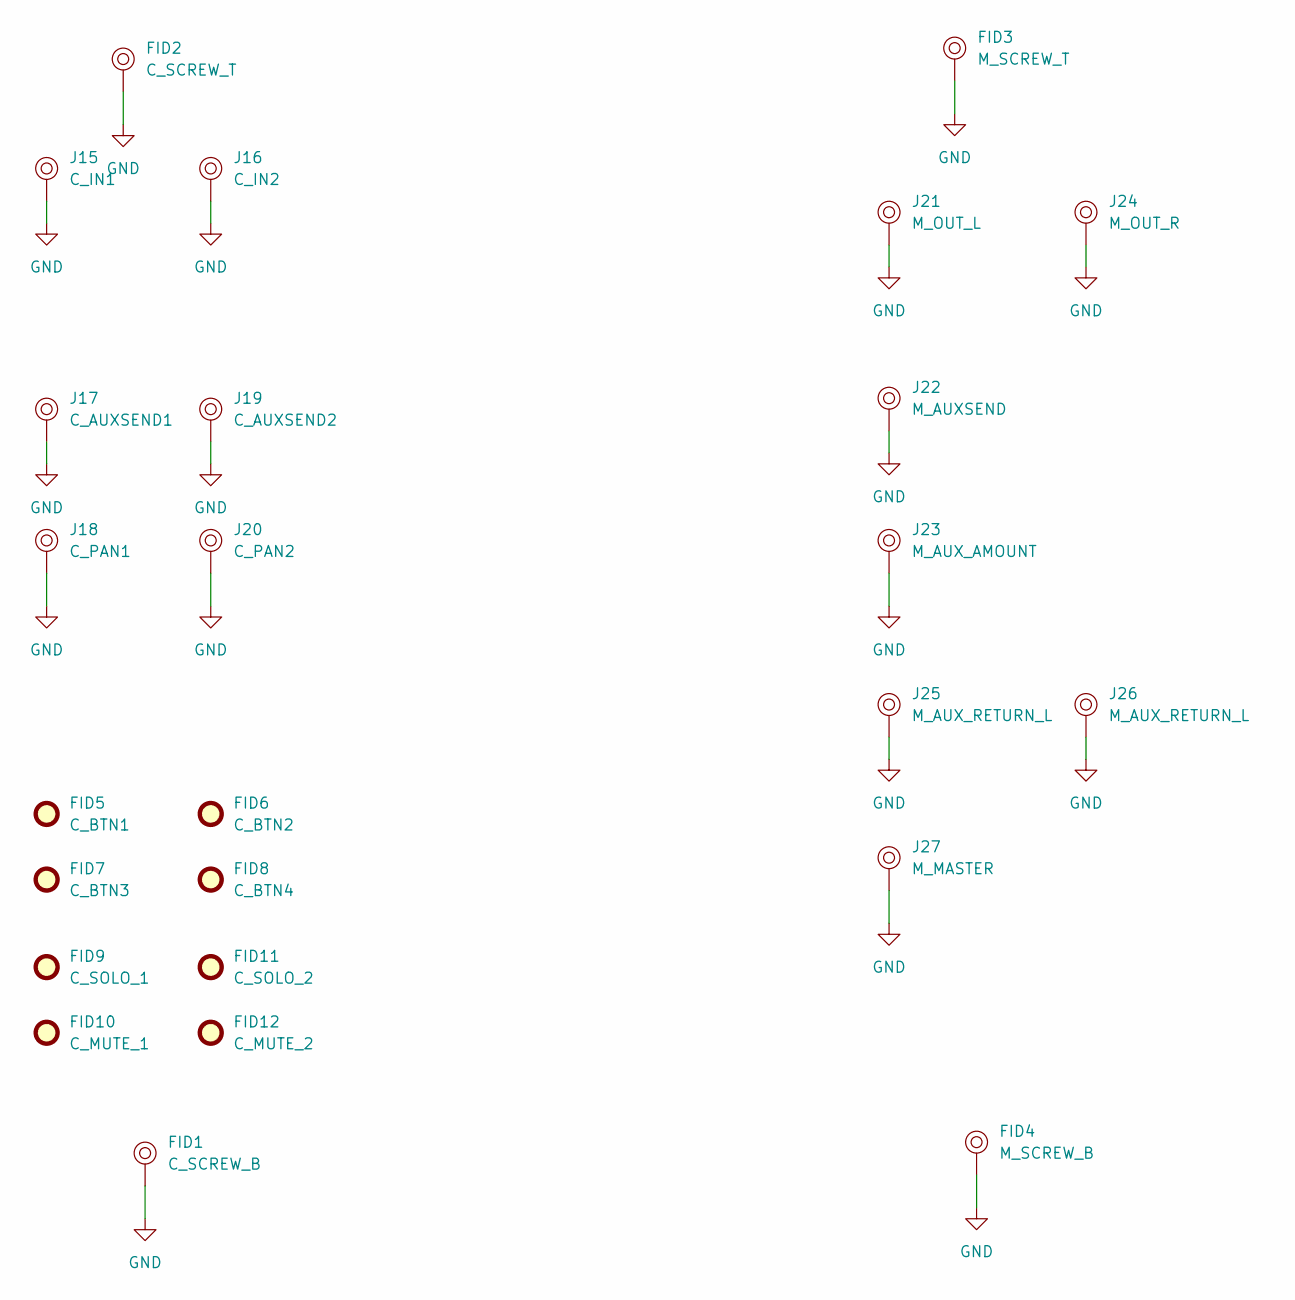
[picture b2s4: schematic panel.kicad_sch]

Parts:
FID1: C_SCREW_B; eurorack_screw_hole
FID2: C_SCREW_T; eurorack_screw_hole
FID3: M_SCREW_T; eurorack_screw_hole
FID4: M_SCREW_B; eurorack_screw_hole
FID5: C_BTN1; toggle_sw_hole
FID6: C_BTN2; toggle_sw_hole
FID7: C_BTN3; toggle_sw_hole
FID8: C_BTN4; toggle_sw_hole
FID9: C_SOLO_1; SOLO_CUTOUT
FID10: C_MUTE_1; MUTE_CUTOUT
FID11: C_SOLO_2; SOLO_CUTOUT
FID12: C_MUTE_2; MUTE_CUTOUT
J15: C_IN1; thonkiconn_hole
J16: C_IN2; thonkiconn_hole
J17: C_AUXSEND1; knob_hole
J18: C_PAN1; knob_hole
J19: C_AUXSEND2; knob_hole
J20: C_PAN2; knob_hole
J21: M_OUT_L; thonkiconn_hole
J22: M_AUXSEND; thonkiconn_hole
J23: M_AUX_AMOUNT; knob_hole
J24: M_OUT_R; thonkiconn_hole
J25, J26: M_AUX_RETURN_L; thonkiconn_hole
J27: M_MASTER; knob_hole

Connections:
GND: FID1.1, FID2.1, FID3.1, FID4.1, J15.1, J16.1, J17.1, J18.1, J19.1, J20.1, J21.1, J22.1, J23.1, J24.1, J25.1, J26.1, J27.1; also elsewhere on the board
